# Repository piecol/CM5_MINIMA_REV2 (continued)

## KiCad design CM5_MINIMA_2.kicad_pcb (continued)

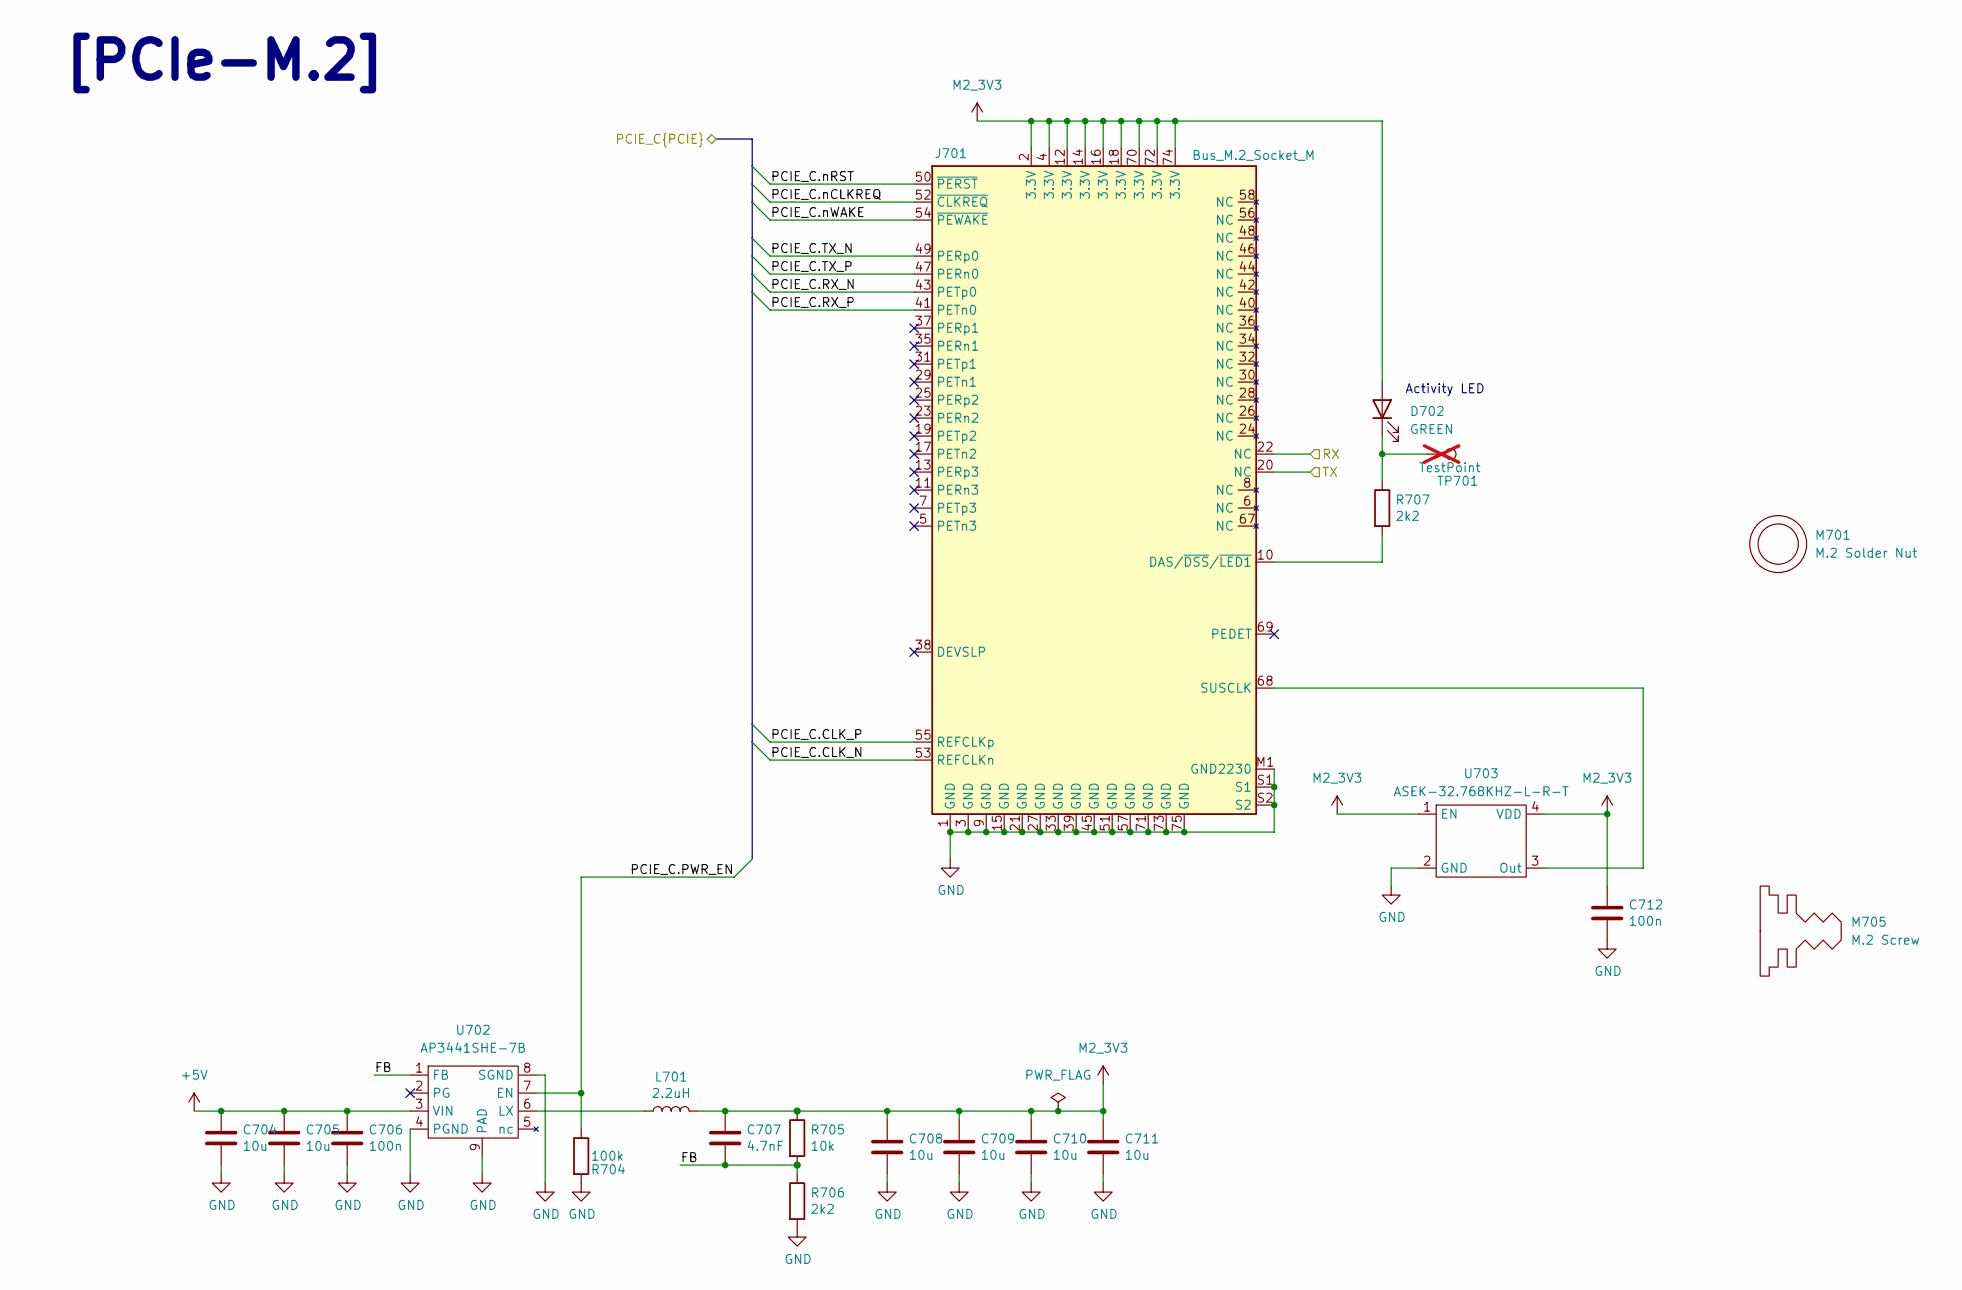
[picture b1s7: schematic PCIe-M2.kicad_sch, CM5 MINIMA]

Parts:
C704, C705, C708, C709, C710, C711: 10u; C_0805_2012Metric; Part Description 10uF 10% 10V Ceramic Capacitor X7R 0805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
C706, C712: 100n; C_0402_1005Metric; Part Description 0.1uF 10% 16V Ceramic Capacitor X7R 040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
C707: 4.7nF; C_0402_1005Metric; Part Description 4.7nF capacitor 0402
D702: GREEN; LED-SMD_L1.7-W0.6-RD
J701: Bus_M.2_Socket_M; M.2 M Key socket 2230; Part Description M.2 M Key connector
L701: 2.2uH; L_Bourns_SRP5030CC; Part Description Inductor, SMT, 2520, 2u2, IRMS=7A, ISAT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
M701: M.2 Solder Nut; MountingHole_3.78mm_M2_Pad_TopOnly; Part Description Solder nut for M.2 slot
M705: M.2 Screw; Part Description M.2 Screw
R704: 100k; R_0402_1005Metric
R705: 10k; R_0402_1005Metric
R706: 2k2; R_0402_1005Metric
R707: 2k2; R_0402_1005Metric; Part Description Resistor 1K M1005 1% 63mW
TP701: TestPoint; TestPoint_Pad_2.0x2.0mm; Part Description Test point; not fitted
U702: AP3441SHE-7B; DFN-8-1EP_2x2mm_P0.5mm_EP1.05x1.75mm; Part Description 3A DC-DC converter
U703: ASEK-32.768KHZ-L-R-T; Crystal_SMD_3225-4Pin_3.2x2.5mm; Part Description 32KHz Xtal oscilator

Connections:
+5V: C704.1, C705.1, C706.1, U702.3 (VIN); also elsewhere on the board
/CM5/PCIE_PI.CLK_N: J701.53 (REFCLKn); also elsewhere on the board
/CM5/PCIE_PI.CLK_P: J701.55 (REFCLKp); also elsewhere on the board
/CM5/PCIE_PI.PWR_EN: R704.1, U702.7 (EN); also elsewhere on the board
/CM5/PCIE_PI.RX_N: J701.43 (PETp0); also elsewhere on the board
/CM5/PCIE_PI.RX_P: J701.41 (PETn0); also elsewhere on the board
/CM5/PCIE_PI.TX_N: J701.49 (PERp0); also elsewhere on the board
/CM5/PCIE_PI.TX_P: J701.47 (PERn0); also elsewhere on the board
/CM5/PCIE_PI.nCLKREQ: J701.52 (~CLKREQ); also elsewhere on the board
/CM5/PCIE_PI.nRST: J701.50 (~PERST); also elsewhere on the board
/CM5/PCIE_PI.nWAKE: J701.54 (~PEWAKE); also elsewhere on the board
/PCIe-M2/FB: C707.2, R705.2, R706.1, U702.1 (FB)
/PCIe-M2/RX: J701.22 (NC); also elsewhere on the board
/PCIe-M2/TX: J701.20 (NC); also elsewhere on the board
GND: C704.2, C705.2, C706.2, C708.2, C709.2, C710.2, C711.2, C712.2, J701.1 (GND), J701.3 (GND), J701.9 (GND), J701.15 (GND), J701.21 (GND), J701.27 (GND), J701.33 (GND), J701.39 (GND), J701.45 (GND), J701.51 (GND), J701.57 (GND), J701.71 (GND), J701.73 (GND), J701.75 (GND), J701.M1 (GND2230), J701.S1, J701.S2, R704.2, R706.2, U702.4 (PGND), U702.8 (SGND), U702.9 (PAD), U703.2 (GND); also elsewhere on the board
M2_3V3: C707.1, C708.1, C709.1, C710.1, C711.1, C712.1, D702.2 (A), J701.2 (3.3V), J701.4 (3.3V), J701.12 (3.3V), J701.14 (3.3V), J701.16 (3.3V), J701.18 (3.3V), J701.70 (3.3V), J701.72 (3.3V), J701.74 (3.3V), L701.2, R705.1, U703.1 (EN), U703.4 (VDD)
unnamed: D702.1 (K), R707.1, TP701.1
unnamed: J701.10 (DAS/~DSS/~LED1), R707.2
unnamed: J701.68 (SUSCLK), U703.3 (Out)
unnamed: L701.1, U702.6 (LX)

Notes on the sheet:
[PCIe-M.2]
Activity LED

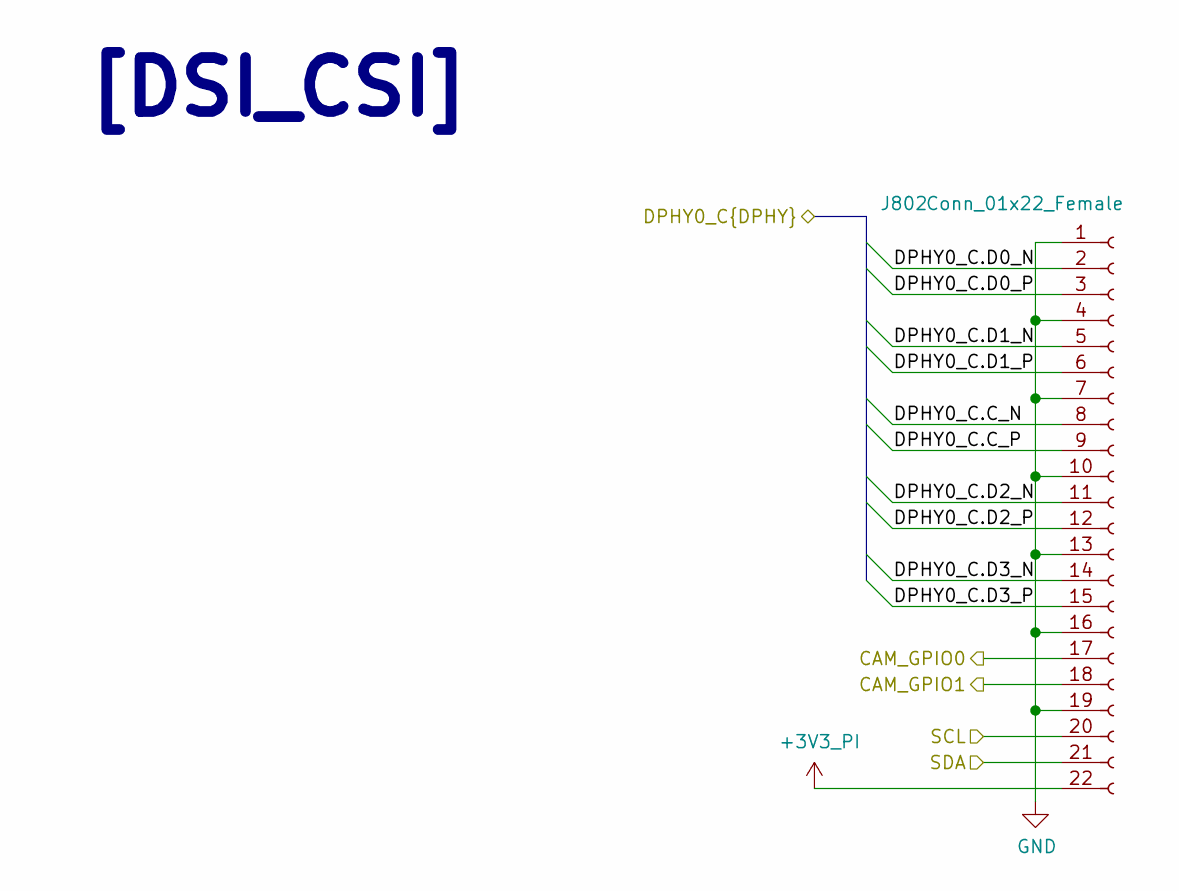
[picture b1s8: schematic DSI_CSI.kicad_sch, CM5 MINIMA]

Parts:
J802: Conn_01x22_Female; Hirose_FH12-22S-0.5SH_1x22-1MP_P0.50mm_Horizontal; Part Description 22 Position FFC, FPC Connector Contacts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

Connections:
+3V3_PI: J802.22; also elsewhere on the board
/CM5/CAM_GPIO0: J802.17; also elsewhere on the board
/CM5/CAM_GPIO1: J802.18; also elsewhere on the board
/CM5/DPHY0_P.C_N: J802.8; also elsewhere on the board
/CM5/DPHY0_P.C_P: J802.9; also elsewhere on the board
/CM5/DPHY0_P.D0_N: J802.2; also elsewhere on the board
/CM5/DPHY0_P.D0_P: J802.3; also elsewhere on the board
/CM5/DPHY0_P.D1_N: J802.5; also elsewhere on the board
/CM5/DPHY0_P.D1_P: J802.6; also elsewhere on the board
/CM5/DPHY0_P.D2_N: J802.11; also elsewhere on the board
/CM5/DPHY0_P.D2_P: J802.12; also elsewhere on the board
/CM5/DPHY0_P.D3_N: J802.14; also elsewhere on the board
/CM5/DPHY0_P.D3_P: J802.15; also elsewhere on the board
/SCL: J802.20; also elsewhere on the board
/SDA: J802.21; also elsewhere on the board
GND: J802.1, J802.4, J802.7, J802.10, J802.13, J802.16, J802.19; also elsewhere on the board

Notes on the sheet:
[DSI_CSI]

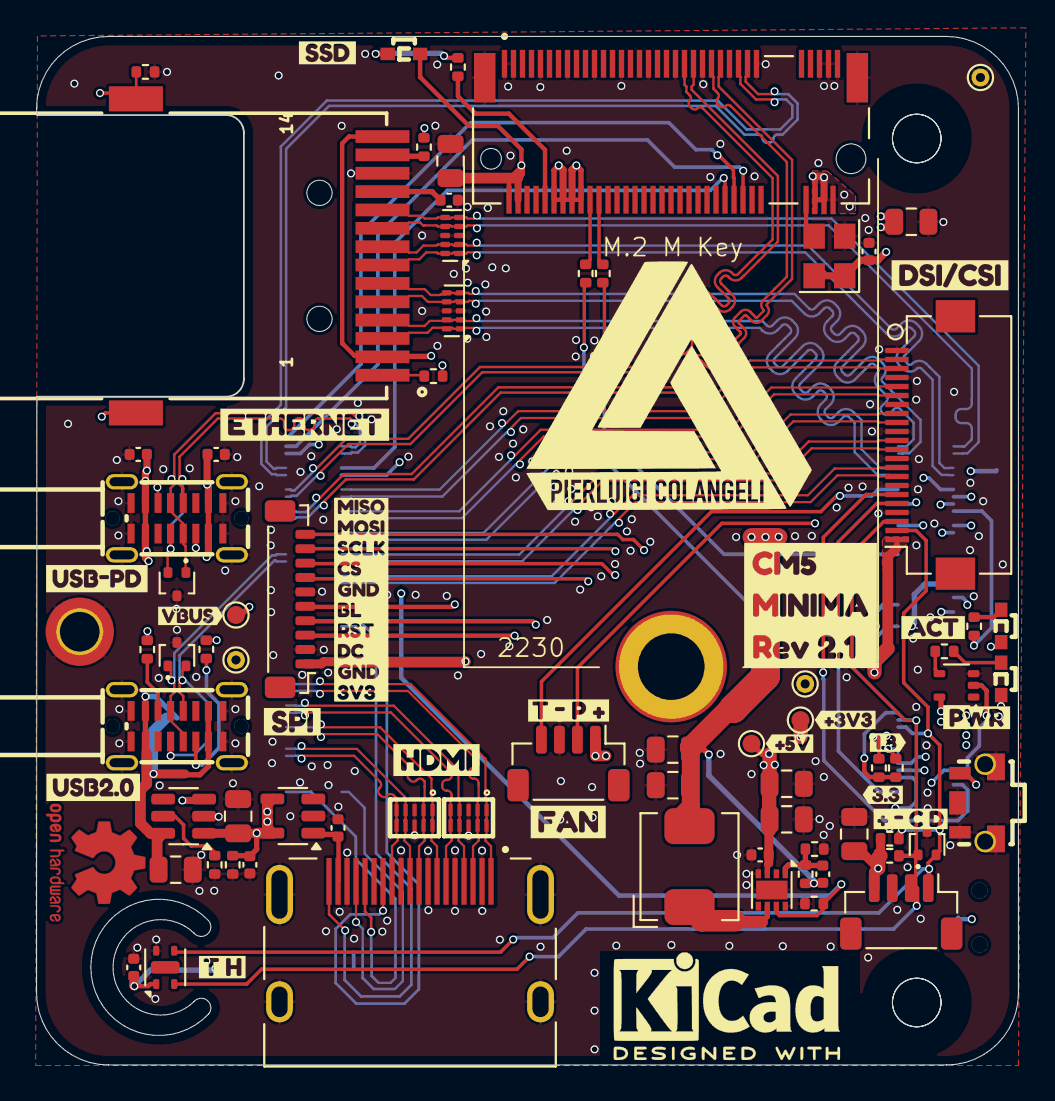
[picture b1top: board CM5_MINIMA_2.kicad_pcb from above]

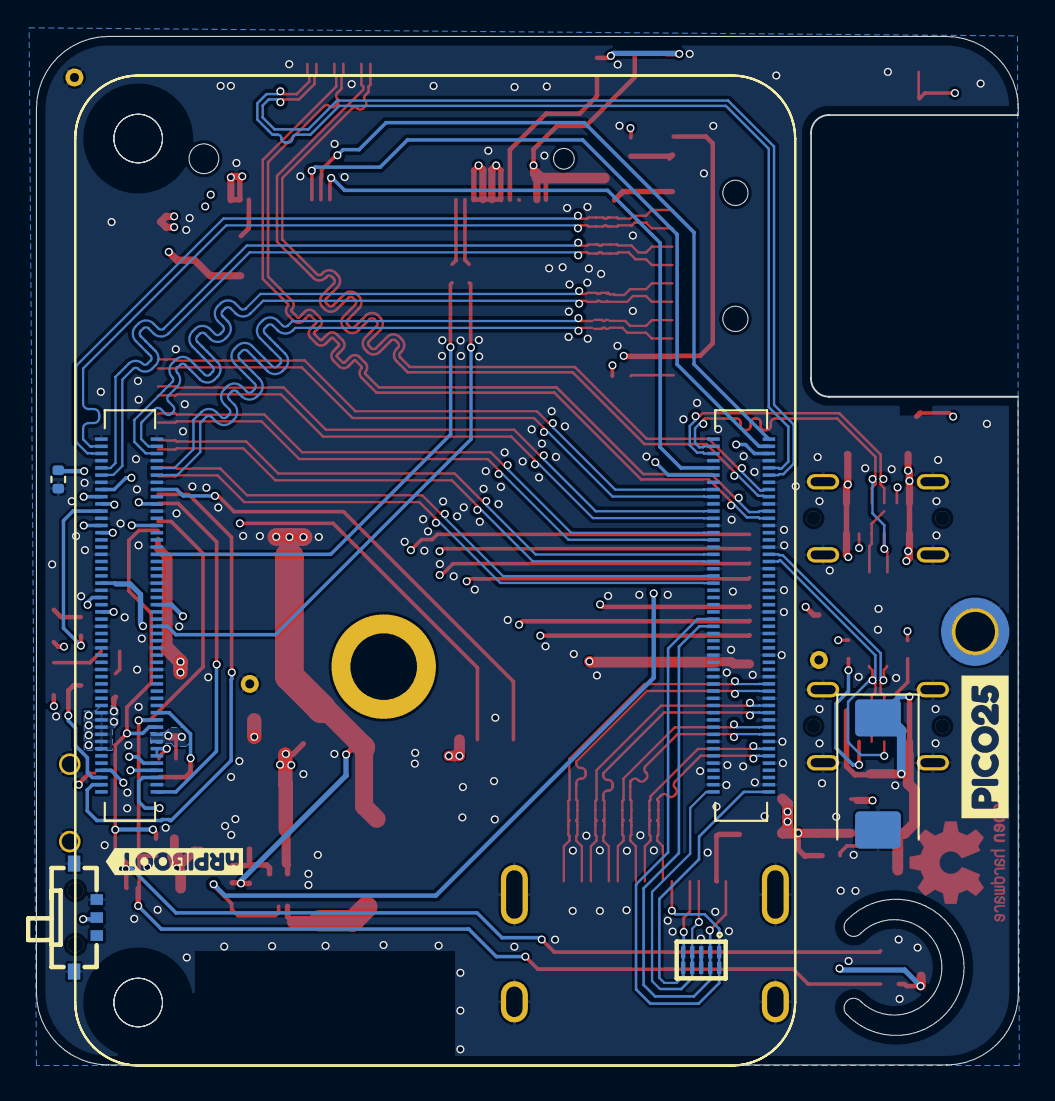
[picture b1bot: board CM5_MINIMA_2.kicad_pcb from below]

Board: 6 copper layers, 54.6 x 57.1 mm, 100 parts (8 on the bottom side), 94 nets.

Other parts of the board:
kibuzzard-675DA838: G***; kibuzzard-675DA838
kibuzzard-675DA850: G***; kibuzzard-675DA850
kibuzzard-675DA866: G***; kibuzzard-675DA866
kibuzzard-675EDCA4: G***; kibuzzard-675EDCA4
kibuzzard-675EDCB9: G***; kibuzzard-675EDCB9
kibuzzard-679BB153: G***; kibuzzard-679BB153
kibuzzard-6772D327: G***; kibuzzard-6772D327
kibuzzard-6772DA33: G***; kibuzzard-6772DA33
kibuzzard-6773B9B9: G***; kibuzzard-6773B9B9
kibuzzard-6773B9CA: G***; kibuzzard-6773B9CA
kibuzzard-6773B9F7: G***; kibuzzard-6773B9F7
kibuzzard-6773BA43: G***; kibuzzard-6773BA43
kibuzzard-6773BA89: G***; kibuzzard-6773BA89
kibuzzard-6773C2D7: G***; kibuzzard-6773C2D7
kibuzzard-6773C222: G***; kibuzzard-6773C222
kibuzzard-6773C376: G***; kibuzzard-6773C376
kibuzzard-6773CC4D: G***; kibuzzard-6773CC4D
kibuzzard-6773CC39: G***; kibuzzard-6773CC39
kibuzzard-6775AD68: G***; kibuzzard-6775AD68
kibuzzard-67758845: G***; kibuzzard-67758845
kibuzzard-67758943: G***; kibuzzard-67758943
kibuzzard-67795592: G***; kibuzzard-67795592

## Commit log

2025-01-04 power symbols
2025-01-04 pcie signal corrected
2025-01-04 save
2025-01-04 drc ok
2025-01-04 changed i2c connector and nrpiboot
2025-01-04 m2 vin increased size
2025-01-04 chore
2025-01-04 esd HDMI complete
2025-01-04 more GND vias
2025-01-04 BOM ok
2025-01-04 pcbway prod files created
2025-01-04 schematics
2025-01-04 pics
2025-01-04 pcb pic
2025-01-04 save and exit
2025-01-06 HDMI impedance 100ohm fix reroute
2025-01-06 pcbway redraw
2025-01-08 exit
2025-01-14 swap TX RX M2
2025-01-14 polish
2025-01-17 fixed PN on M.2 connector
2025-01-30 rework for JLC
2025-02-03 prod
2025-02-13 jlc bom polishing
2025-02-26 Update .gitignore
    Ignore macOS Finder metadata (.DS_Store)
2025-03-22 3d models updated
2025-03-22 save exit
2025-03-22 updated semantic versioning
2025-03-28 check BOM
